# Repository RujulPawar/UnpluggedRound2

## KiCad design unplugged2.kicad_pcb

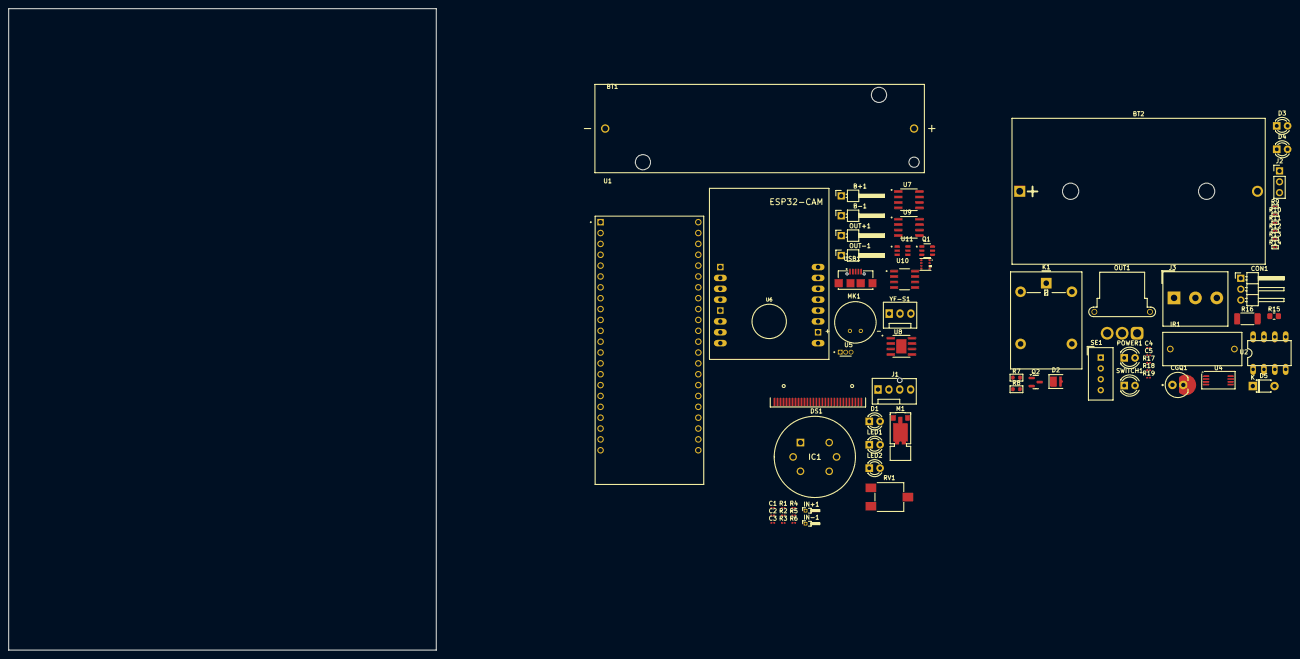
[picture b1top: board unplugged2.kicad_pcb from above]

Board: 2 copper layers, 100.0 x 150.0 mm, 70 parts (0 on the bottom side), 45 nets, no tracks yet.

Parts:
B+1: Header-Male-2.54_1x1; PinHeader_1x01_P2.54mm_Horizontal
B-1: Header-Male-2.54_1x1; PinHeader_1x01_P2.54mm_Horizontal
BT1: 1043; BAT_1043
BT2: Battery; BatteryHolder_Bulgin_BX0036_1xC
C1, C2, C4, C5: 100nF; C_0201_0603Metric
C3: 10uF; C_0201_0603Metric
CGQ1: PT333-3B; pt333
CON1: 53014-0510; PinHeader_1x03_P2.54mm_Horizontal
D1, D3, D4: LED; LED_D3.0mm
D2: LED; LED_Luminus_MP-3030-1100_3.0x3.0mm
D5: D; D_T-1_P5.08mm_Horizontal
DS1: OLED-128O064D
IC1: MQ135
IN+1: Header-Male-2.54_1x1; PinHeader_1x01_P1.00mm_Horizontal
IN-1: Header-Male-2.54_1x1; PinHeader_1x01_P1.00mm_Horizontal
IR1: IR333C/H0/L10; ir333
J1: Conn_01x04; FanPinHeader_1x04_P2.54mm_Vertical
J2: input signal; PinHeader_1x03_P2.54mm_Vertical
J3: Screw_Terminal_01x03; Altech_AK300_1x03_P5.00mm_45-Degree
K1: Relay_SPDT; Relay_SPDT_Omron-G5LE-1
LED1: GREEN; LED_D3.0mm
LED2: RED; LED_D3.0mm
M1: Motor_Servo; Vybronics_VZ30C1T8219732L
MK1: Microphone_Condenser; mic
OUT1: A2541WR-3P; AMASS_MR30PW-FB_1x03_P3.50mm_Horizontal
OUT+1: Header-Male-2.54_1x1; PinHeader_1x01_P2.54mm_Horizontal
OUT-1: Header-Male-2.54_1x1; PinHeader_1x01_P2.54mm_Horizontal
POWER1: RED; LED_D4.0mm
Q1: FS8205; fs
Q2: Q_NPN_BCE; SOT-23
R1: 10k; R_0201_0603Metric
R2, R3, R5: 1K; R_0201_0603Metric
R4: 1.2KΩ; R_0201_0603Metric
R6, R11: 100Ω; R_0201_0603Metric
R7: 2K; R_0603_1608Metric
R8: 100K; R_0603_1608Metric
R9, R14: 1KΩ; R_0201_0603Metric
R10, R12, R13: 10KΩ; R_0201_0603Metric
R15: 4.7k; R_0805_2012Metric_Pad1.20x1.40mm_HandSolder
R16: 1K; R_2010_5025Metric_Pad1.40x2.65mm_HandSolder
R17, R18, R19: R; R_0201_0603Metric
RV1: POT_TRIM; Potentiometer_ACP_CA6-VSMD_Vertical
SE1: DHT11; Aosong_DHT11_5.5x12.0_P2.54mm
SWITCH1: RED; LED_D4.0mm
U1: ESP32-S3-DEVKITC-1-N8R2; esp32
U2: MAX471; DIL08
U3: BME280; PSON65P250X250X100-8N
U4: LM393; SSOP-8_4.4x3.5mm_P0.65mm
U5: MLX90217LUA-CAA-000-BU; hall_effect
U6: ESP32-CAM
U7: INA219BID; SOIC127P599X175-8N
U8: TP4056; tp
U9: LMV393; Lmv
U10: MCP6562; mcp
U11: DW01A; DW
USB1: MicroUSB; usb
YF-S1: FanPinHeader_1x03_P2.54mm_Vertical

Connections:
+VCC: U9.8 (V+), U10.8 (V+)
-VCC: U9.4 (V-), U10.4 (V-)
/3.3V: CON1.3, D2.1 (A), R15.2, SE1.1 (Vcc)
/COM: J3.2, K1.1
/Data: CON1.2, R15.1, SE1.2 (Data)
/NC: J3.1, K1.4
/NO: J3.3, K1.3
/Signal: J2.2, R19.1
DO: OUT1.1, R13.1, R14.1, U4.7
Discharge: R8.2, U2.5 (SIGN)
GND: BT2.2 (-), C1.1, C3.1, C4.1, C5.1, CGQ1.1 (E), CON1.1, D1.1 (K), D3.1 (K), IN-1.1, IR1.1 (C), J1.2, J2.1, OUT1.2, OUT-1.1, Q1.1 (S1), Q2.3 (E), R4.2, R5.1, R7.2, R9.1, R10.1, R16.1, RV1.3, SE1.4 (GND), U2.1 (SHDN), U2.4 (GND), U4.4 (GND), U8.1 (TEMP), U8.3 (GND), USB1.5
Load: U2.6 (RS-), U2.7 (RS-)
unnamed: BT2.1 (+), U2.2 (RS+), U2.3 (RS+)
unnamed: C5.2, CGQ1.2 (C), R12.1, U4.5
unnamed: D1.2 (A), J1.4, U9.1
unnamed: D2.2 (K), R16.2
unnamed: D3.2 (A), R17.2
unnamed: D4.2 (A), R18.2
unnamed: D4.1 (K), D5.2 (A), K1.2, Q2.2 (C)
unnamed: DS1.1 (GND), DS1.30 (GND)
unnamed: IR1.2 (A), R11.1
unnamed: J1.3, R1.1, R1.2, U10.3 (+)
unnamed: C1.2, IN+1.1, LED1.1 (A), LED2.1 (A), U8.4 (VCC), U8.8 (CE), USB1.1
unnamed: LED1.2 (K), R2.1
unnamed: LED2.2 (K), R3.2
unnamed: POWER1.2 (K), R9.2
unnamed: Q1.6 (G1), U11.3 (OC)
unnamed: Q1.4 (G2), U11.1 (OD)
unnamed: B-1.1, C2.2, Q1.3 (S2), U11.6 (GND)
unnamed: Q2.1 (B), R19.2
unnamed: R10.2, U4.2
unnamed: R14.2, SWITCH1.2 (K)
unnamed: U1.J1_1 (3V3), U1.J1_2 (3V3)
unnamed: U1.J1_22 (GND), U1.J3_1 (GND), U1.J3_21 (GND), U1.J3_22 (GND)
unnamed: U3.1 (GND), U3.7 (GND)
unnamed: B+1.1, C3.2, OUT+1.1, R6.2, U8.5 (BAT)
unnamed: R3.1, U8.7 (CHRG)
unnamed: R4.1, U8.2 (PROG)
unnamed: R2.2, U8.6 (STDBY)
unnamed: U9.2 (_), U10.1
unnamed: RV1.2, U9.3 (+), U10.2 (_)
unnamed: R5.2, U11.2 (CS)
unnamed: C2.1, R6.1, U11.5 (VCC)
VCC: C4.2, D5.1 (K), J1.1, J2.3, K1.5, OUT1.3, POWER1.1 (A), R11.2, R12.2, R13.2, R17.1, R18.1, RV1.1, SWITCH1.1 (A), U4.8 (VDD)
Vout: R7.1, U2.8 (OUT)
